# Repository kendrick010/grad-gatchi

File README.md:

# grad-gatchi

> Did not implement the Piezo Buzzer feature but feel to add so. 

BOM: https://octopart.com/bom-tool/EEuozXCZ

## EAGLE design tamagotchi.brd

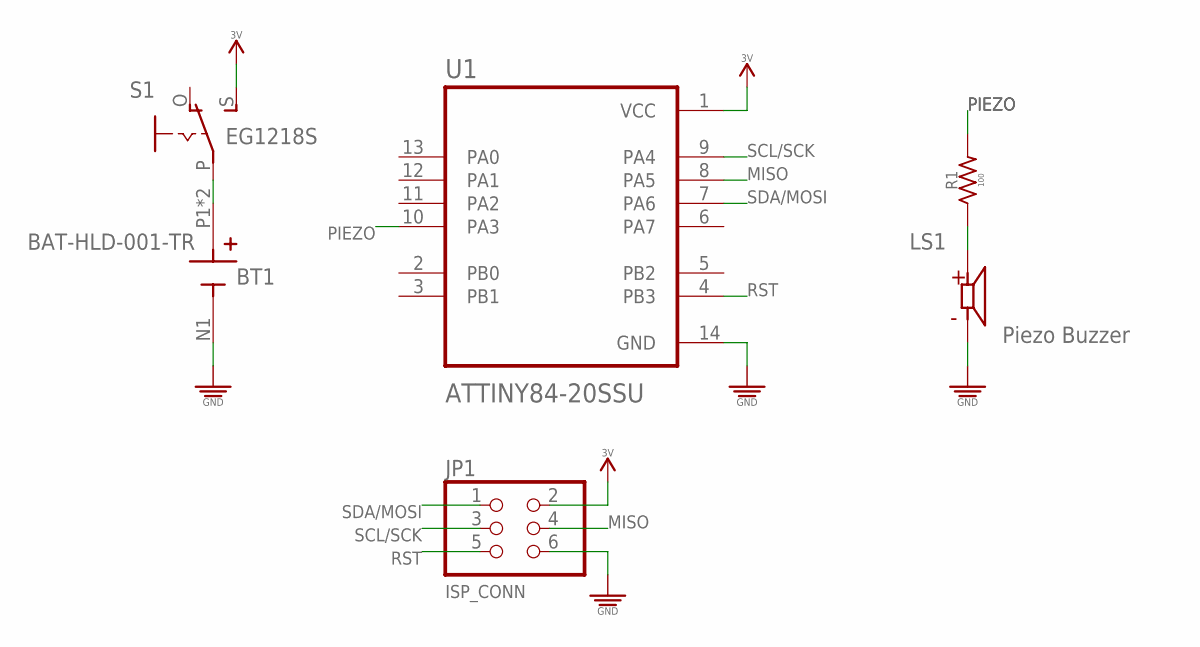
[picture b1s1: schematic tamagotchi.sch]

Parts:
BT1: BAT-HLD-001-TR; BAT_BAT-HLD-001-TR
JP1: PINHD-2X3; 2X03
LS1: Piezo Buzzer; CUI_CSS-0575A-SMT
R1: 100; RESC2012X60_SMD-0805
S1: EG1218S; EG1218
U1: ATTINY84-20SSU; SOIC127P600X175-14N

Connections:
3V: JP1.2, S1.S, U1.1 (VCC)
GND: BT1.N1 (-), JP1.6, LS1.2 (N), U1.14 (GND)
MISO: JP1.4, U1.8 (PA5)
unnamed: LS1.1, R1.1
unnamed: BT1.P1 (+), BT1.P2 (+), S1.P
PIEZO: R1.2, U1.10 (PA3)
RST: JP1.5, U1.4 (PB3)
SCL/SCK: JP1.3, U1.9 (PA4)
SDA/MOSI: JP1.1, U1.7 (PA6)

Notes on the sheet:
ISP_CONN

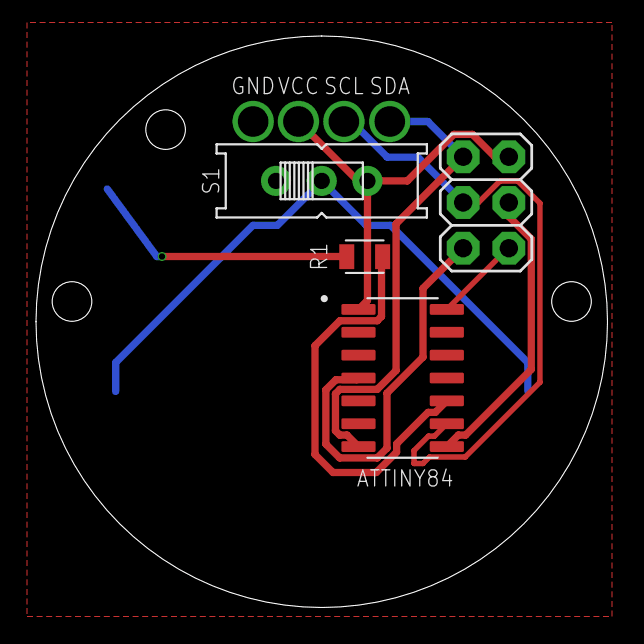
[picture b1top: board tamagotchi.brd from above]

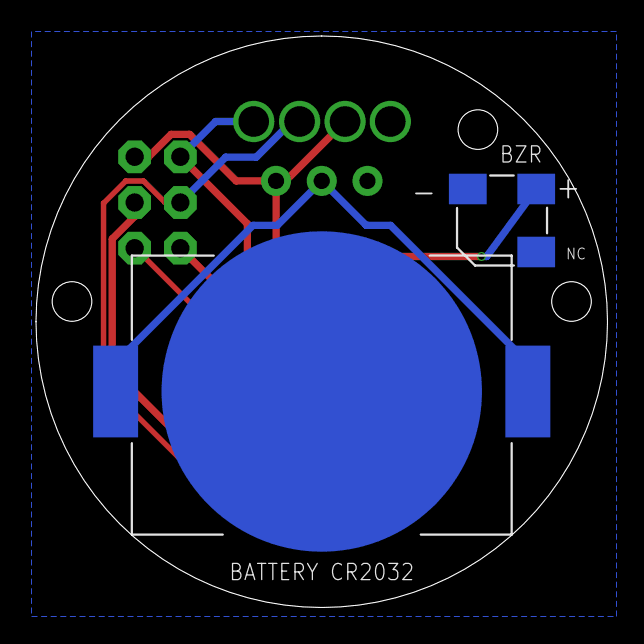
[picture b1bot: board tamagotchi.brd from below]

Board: 2 copper layers, 31.8 x 31.8 mm, 6 parts (2 on the bottom side), 9 nets.

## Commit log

2022-05-23 ecad
2022-05-23 step file
2022-05-24 gerber
2022-06-10 code, updated brd
